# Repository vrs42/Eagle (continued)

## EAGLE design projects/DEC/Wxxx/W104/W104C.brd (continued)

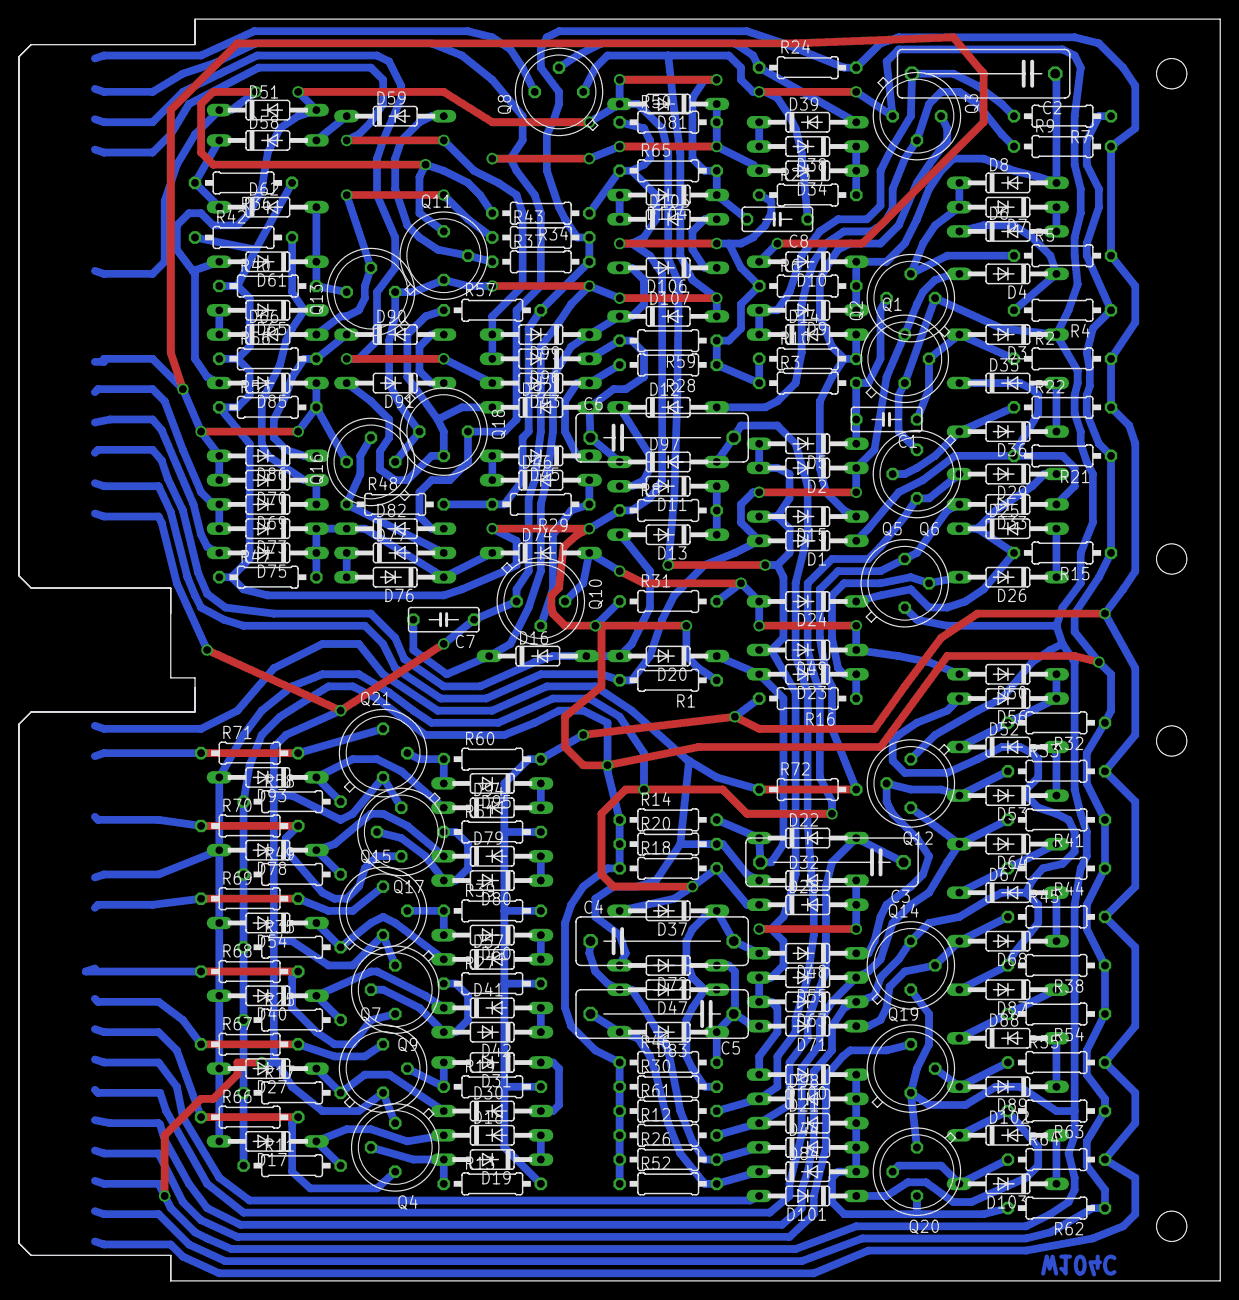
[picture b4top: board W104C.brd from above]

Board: 2 copper layers, 125.7 x 132.1 mm, 211 parts (0 on the bottom side), 105 nets.

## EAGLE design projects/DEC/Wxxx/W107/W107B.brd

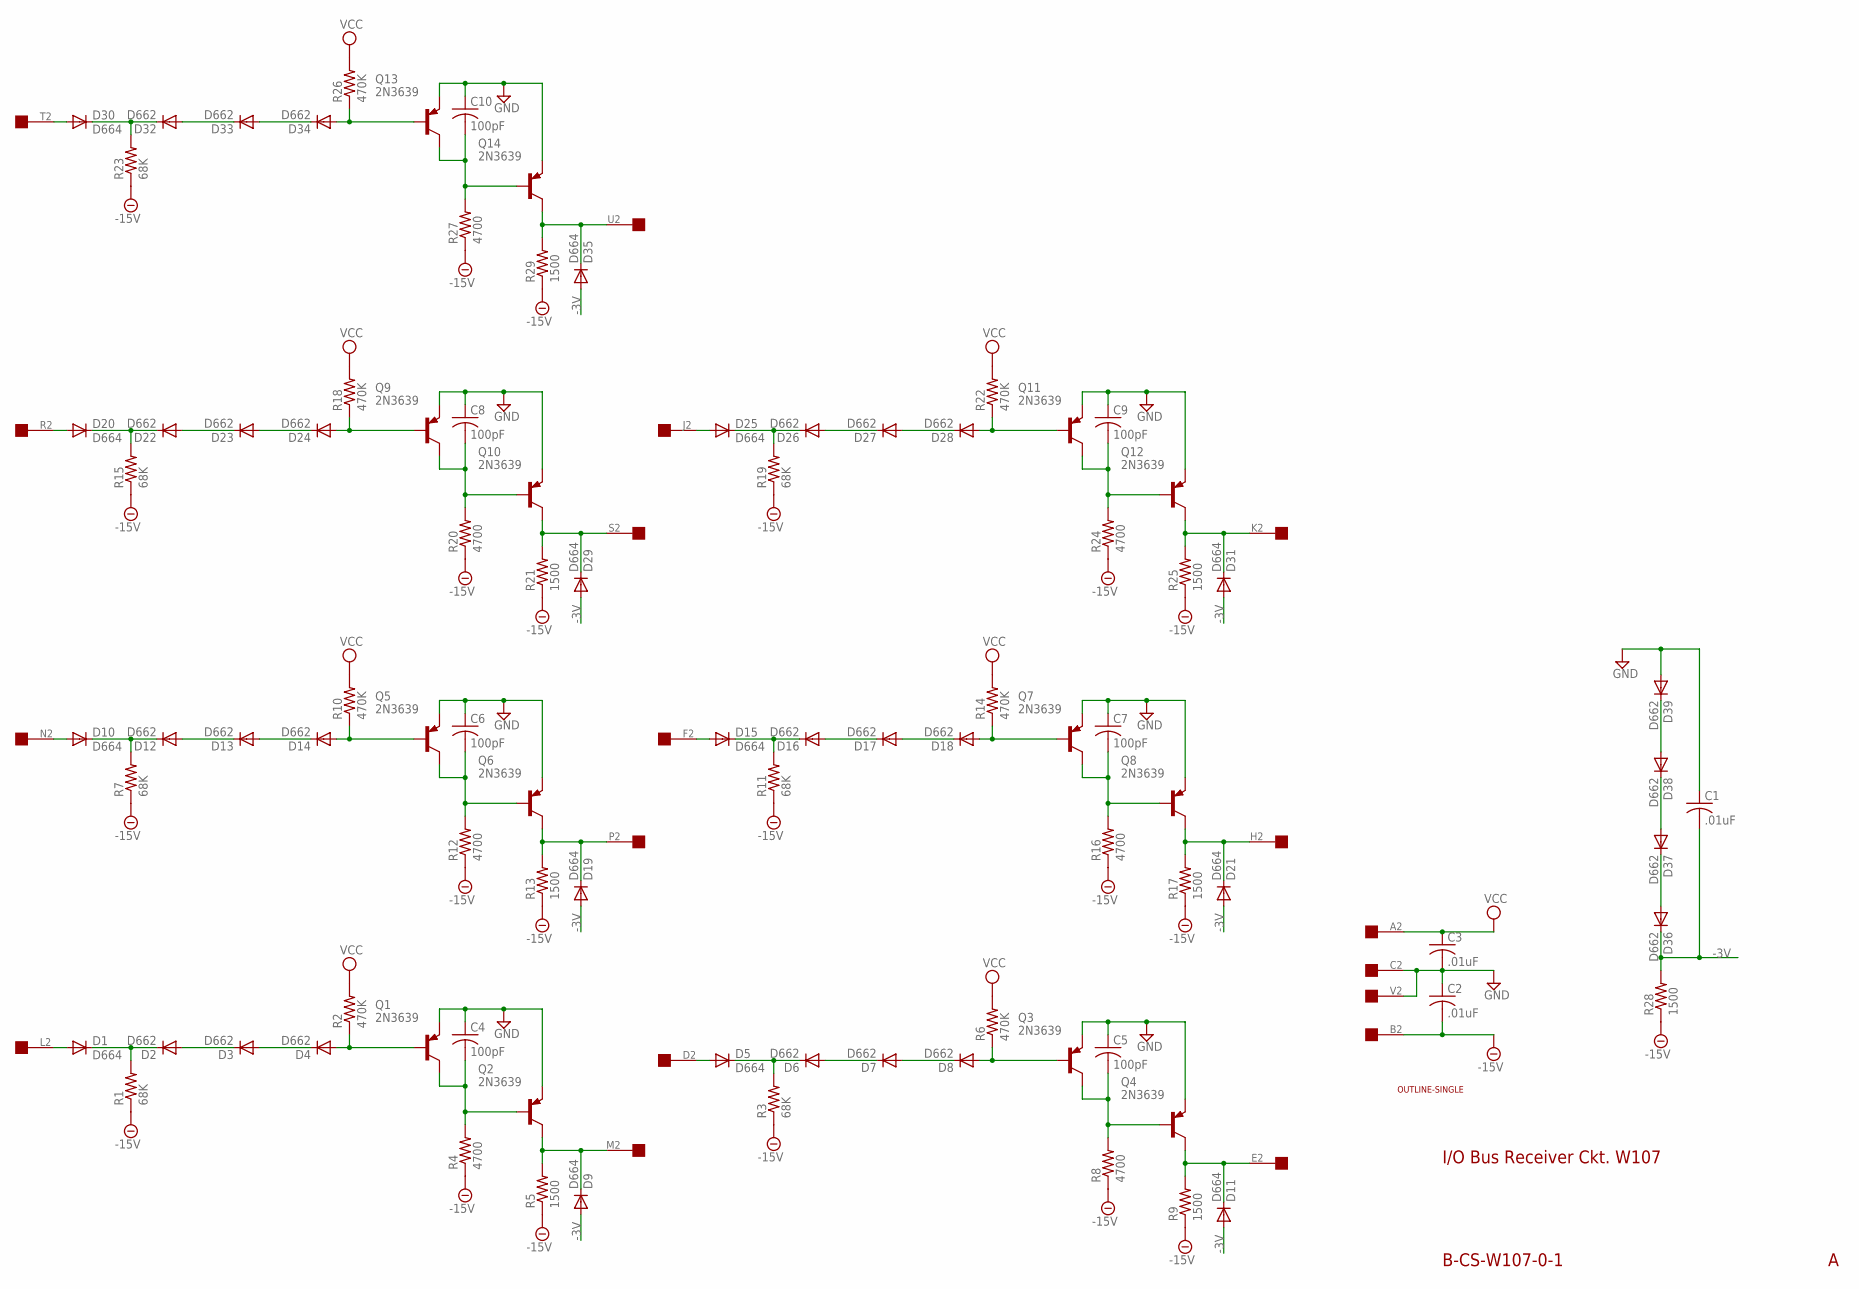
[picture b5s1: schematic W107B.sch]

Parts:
C1, C2, C3: .01uF; C063-025X075
C4, C5, C6, C7, C8, C9, C10: 100pF; C063-025X075
D1, D5, D9, D10, D11, D15, D19, D20, D21, D25, D29, D30, D31, D35: D664; DO35-10
D2, D3, D4, D6, D7, D8, D12, D13, D14, D16, D17, D18, D22, D23, D24, D26, D27, D28, D32, D33, D34, D36, D37, D38, D39: D662; DO35-10
Q1, Q2, Q3, Q4, Q5, Q6, Q7, Q8, Q9, Q10, Q11, Q12, Q13, Q14: 2N3639; TO5
R1, R3, R7, R11, R15, R19, R23: 68K; 0207/10
R2, R6, R10, R14, R18, R22, R26: 470K; 0207/10
R4, R8, R12, R16, R20, R24, R27: 4700; 0207/10
R5, R9, R13, R17, R21, R25, R28, R29: 1500; 0207/10
U$1: OUTLINE-SINGLE; SINGLE
U$2: EDGE-1; EDGE-CON1

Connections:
-3V: C1.2, D9.A, D11.A, D19.A, D21.A, D29.A, D31.A, D35.A, D36.C, R28.2
-15V: C2.2, R1.1, R3.1, R4.1, R5.1, R7.1, R8.1, R9.1, R11.1, R12.1, R13.1, R15.1, R16.1, R17.1, R19.1, R20.1, R21.1, R23.1, R24.1, R25.1, R27.1, R28.1, R29.1, U$2.B2
GND: C1.1, C2.1, C3.2, C4.1, C5.1, C6.1, C7.1, C8.1, C9.1, C10.1, D39.A, Q1.1 (E), Q2.1 (E), Q3.1 (E), Q4.1 (E), Q5.1 (E), Q6.1 (E), Q7.1 (E), Q8.1 (E), Q9.1 (E), Q10.1 (E), Q11.1 (E), Q12.1 (E), Q13.1 (E), Q14.1 (E), U$2.C2, U$2.V2
unnamed: D1.C, D2.C, R1.2
unnamed: D2.A, D3.C
unnamed: D3.A, D4.C
unnamed: D4.A, Q1.2 (B), R2.1
unnamed: D5.C, D6.C, R3.2
unnamed: C4.2, Q1.3 (C), Q2.2 (B), R4.2
unnamed: D9.C, Q2.3 (C), R5.2, U$2.M2
unnamed: D6.A, D7.C
unnamed: D7.A, D8.C
unnamed: D8.A, Q3.2 (B), R6.1
unnamed: C5.2, Q3.3 (C), Q4.2 (B), R8.2
unnamed: D11.C, Q4.3 (C), R9.2, U$2.E2
unnamed: D10.C, D12.C, R7.2
unnamed: D12.A, D13.C
unnamed: D13.A, D14.C
unnamed: D14.A, Q5.2 (B), R10.1
unnamed: C6.2, Q5.3 (C), Q6.2 (B), R12.2
unnamed: D19.C, Q6.3 (C), R13.2, U$2.P2
unnamed: D15.C, D16.C, R11.2
unnamed: D16.A, D17.C
unnamed: D17.A, D18.C
unnamed: D18.A, Q7.2 (B), R14.1
unnamed: C7.2, Q7.3 (C), Q8.2 (B), R16.2
unnamed: D21.C, Q8.3 (C), R17.2, U$2.H2
unnamed: D20.C, D22.C, R15.2
unnamed: D22.A, D23.C
unnamed: D23.A, D24.C
unnamed: D24.A, Q9.2 (B), R18.1
unnamed: C8.2, Q9.3 (C), Q10.2 (B), R20.2
unnamed: D29.C, Q10.3 (C), R21.2, U$2.S2
unnamed: D25.C, D26.C, R19.2
unnamed: D26.A, D27.C
unnamed: D27.A, D28.C
unnamed: D28.A, Q11.2 (B), R22.1
unnamed: C9.2, Q11.3 (C), Q12.2 (B), R24.2
unnamed: D31.C, Q12.3 (C), R25.2, U$2.K2
unnamed: D30.C, D32.C, R23.2
unnamed: D32.A, D33.C
unnamed: D33.A, D34.C
unnamed: D34.A, Q13.2 (B), R26.1
unnamed: C10.2, Q13.3 (C), Q14.2 (B), R27.2
unnamed: D35.C, Q14.3 (C), R29.2, U$2.U2
unnamed: D5.A, U$2.D2
unnamed: D36.A, D37.C
unnamed: D38.A, D39.C
unnamed: D37.A, D38.C
unnamed: D30.A, U$2.T2
unnamed: D20.A, U$2.R2
unnamed: D10.A, U$2.N2
unnamed: D1.A, U$2.L2
unnamed: D15.A, U$2.F2
unnamed: D25.A, U$2.J2
VCC: C3.1, R2.2, R6.2, R10.2, R14.2, R18.2, R22.2, R26.2, U$2.A2

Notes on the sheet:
B-CS-W107-0-1
I/O Bus Receiver Ckt. W107

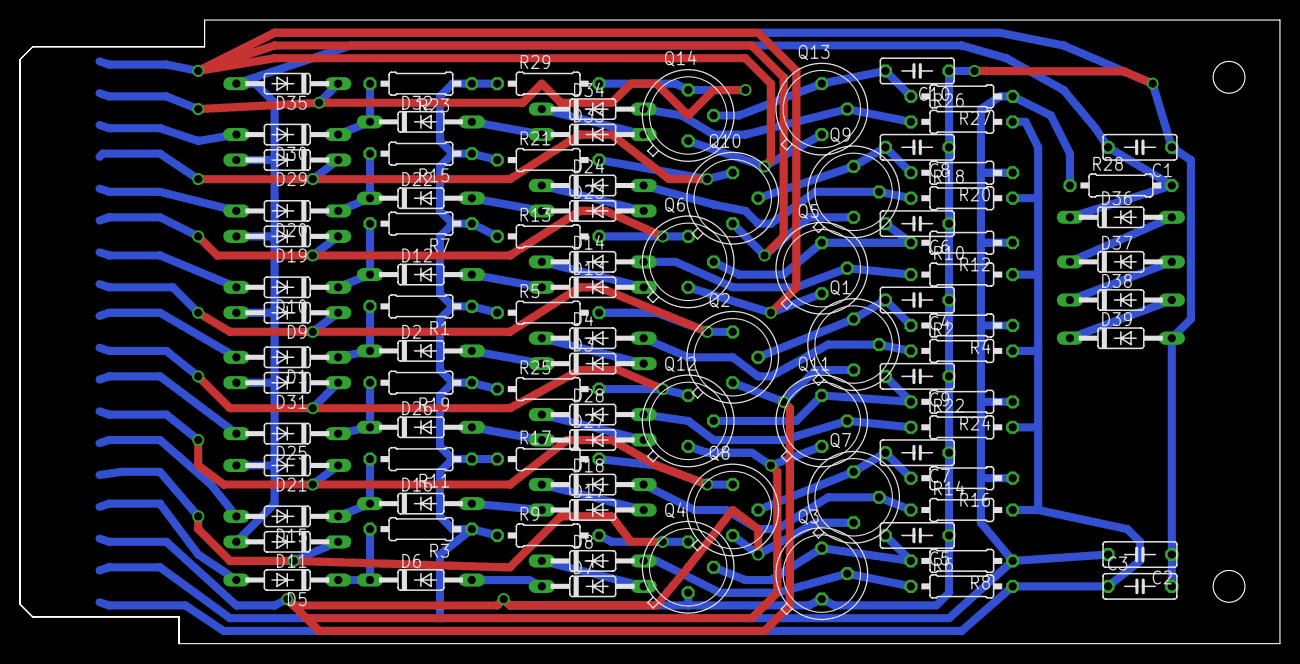
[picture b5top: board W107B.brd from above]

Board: 2 copper layers, 125.7 x 62.2 mm, 94 parts (0 on the bottom side), 56 nets.
